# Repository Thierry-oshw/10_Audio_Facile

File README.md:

# 10_Audio_Facile

Le module Audio_Facile permet d'amplifier un signal électrique analogique pour piloter un haut-parleur.

La licence est celle du CERN Open Hardware Licence version 2; CERN-OHL-P ; permissive.
Le fichier de cette license est présent dans le répertoire: cern_ohl_p_v2.txt

# Photos

# Schéma et fonctionnement

Ci-joint le schéma de la version de 

Le module est basé sur la puce PAM
Il faut l'alimenter avec une tension 5V +-5% (typiquement celle de l'USB classique) sur la pin Vext. (Ne pas oublier GND bien sûr).

## Fonctionnalités
- Petit (23x18 mm)
- Faible coût (2 couches avec composants d'un seul côté)
- Connecteur avec pas de 2.54 mm + empreinte crénelée pour connexion carte à carte

## Outils utilisés

- [Kicad V6](https://www.kicad.org/)

## Fabrication du circuit

Ce circuit a été testé de fond en comble sur de nombreux projets

## Contributeurs

- Thierry Orlandi ([Hardware Freelance](https://www.linkedin.com/in/thierry-orlandi))
- Yohann Belair ([R&D Freelance](https://github.com/ciborg971))

## Licence
[CERN Open Hardware Licence Version 2](https://github.com/Thierry-oshw/10_Audio_Facile/blob/main/LICENSE.txt)

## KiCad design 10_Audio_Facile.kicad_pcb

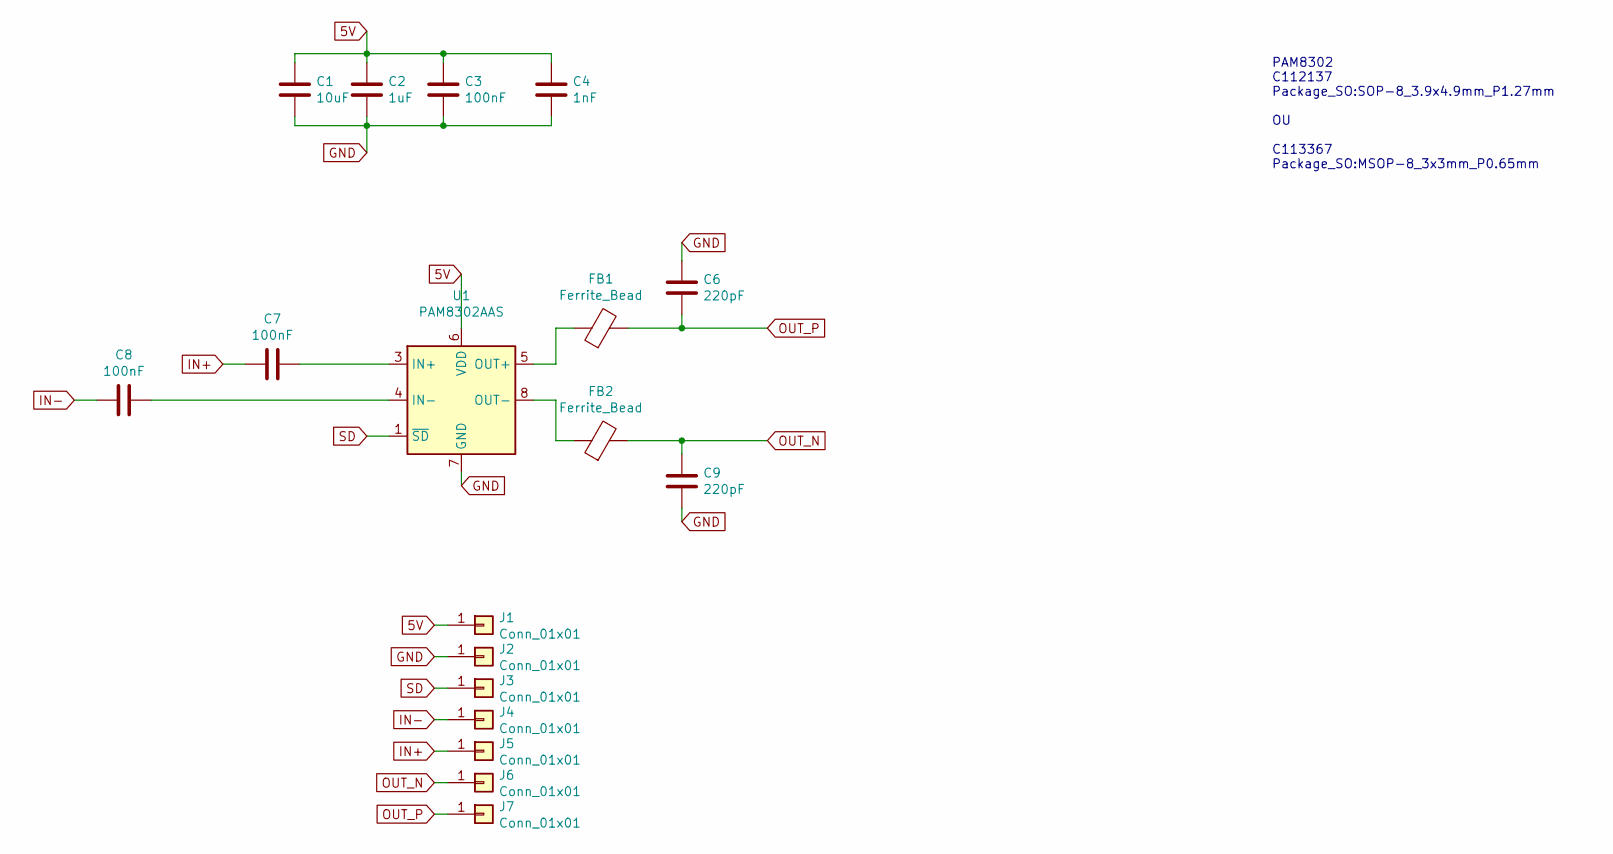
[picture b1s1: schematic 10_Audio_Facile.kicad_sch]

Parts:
C1: 10uF; C_1210_3225Metric; LCSC C39232
C2: 1uF; C_0603_1608Metric; LCSC C15849
C3, C7, C8: 100nF; C_0603_1608Metric; LCSC C14663
C4: 1nF; C_0603_1608Metric; LCSC C1588
C6, C9: 220pF; C_0603_1608Metric; LCSC C1603
FB1, FB2: Ferrite_Bead; L_0603_1608Metric; LCSC C85824
J1, J2, J3, J4, J5, J6, J7: Conn_01x01; Castellated_conn
U1: PAM8302AAS; SOP-8_3.9x4.9mm_P1.27mm; LCSC C112137

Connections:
5V: C1.2, C2.2, C3.2, C4.2, J1.1, U1.6 (VDD)
GND: C1.1, C2.1, C3.1, C4.1, C6.2, C9.1, J2.1, U1.7 (GND)
IN+: C7.2, J5.1
IN-: C8.2, J4.1
unnamed: C7.1, U1.3 (IN+)
unnamed: C8.1, U1.4 (IN-)
unnamed: FB1.1, U1.5 (OUT+)
unnamed: FB2.1, U1.8 (OUT-)
OUT_N: C9.2, FB2.2, J6.1
OUT_P: C6.1, FB1.2, J7.1
SD: J3.1, U1.1 (~SD)

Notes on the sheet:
PAM8302 C112137 Package_SO:SOP-8_3.9x4.9mm_P1.27mm OU C113367 Package_SO:MSOP-8_3x3mm_P0.65mm

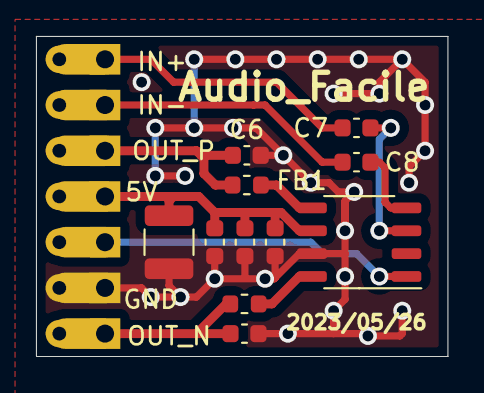
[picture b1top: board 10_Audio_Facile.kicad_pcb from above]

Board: 2 copper layers, 22.9 x 17.8 mm, 18 parts (0 on the bottom side), 11 nets.

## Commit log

2021-04-05 premier jet
2021-05-26 suppression résistances entrées
    schéma et routage à jour
    raf: optimisation taille de la carte
2021-07-24 maj split librairies
2021-08-02 changement date + generation gerber et fichiers de fabrication
2021-09-10 maj partielle à compléter
2021-09-13 Update fp-info-cache
2021-09-14 maj des empreintes pcb
2023-05-02 chgt nom fichier licence
2023-05-18 maj kicad v6
    maj projet
    maj symboles + empreintes
    placement plus compact.
2023-05-19 maj placement routage + fabrication
2023-05-26 ajout in+
2023-05-27 fabrication
2023-05-28 maj readme
